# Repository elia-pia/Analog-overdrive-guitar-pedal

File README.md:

# A compact and easy-to-use analog overdrive guitar pedal.

## Images

Circuit schematic | PCB layout
--- | ---
 | 

## What is this?
 
this is a simple fully analog overdrive pedal that i designed personally, some of the graphics on the pcb are inspire by a Dean From Hell guitar

The goal was to create an affordable and straightforward guitar effect while learning more about analog electronics, audio circuits and PCB design.
it features one tl082 amplifier, two 1N§14B clipping diodes and three gain, tone, volume pots

## Features:

Fully analog signal processing.
TL082 dual operational amplifier.
Two 1N4148 clipping diodes.
Three adjustable controls: Gain, Tone and Volume.
Custom-designed PCB and circuit schematic.
Compact design suitable for a DIY guitar pedal enclosure.
Affordable and beginner-friendly construction.

## Building it

1. Order the PCB from JLCPCB using the KiCad project files.
2. you can build a case with simple household materials or buy a box from an hardware store
3. Assemble the PCB
4. put the pcb in the case

## Cost Estimate

The estimated cost of building one pedal is approximately $50 or less. Actual costs may vary depending on the PCB manufacturer, component availability, enclosure and shipping.

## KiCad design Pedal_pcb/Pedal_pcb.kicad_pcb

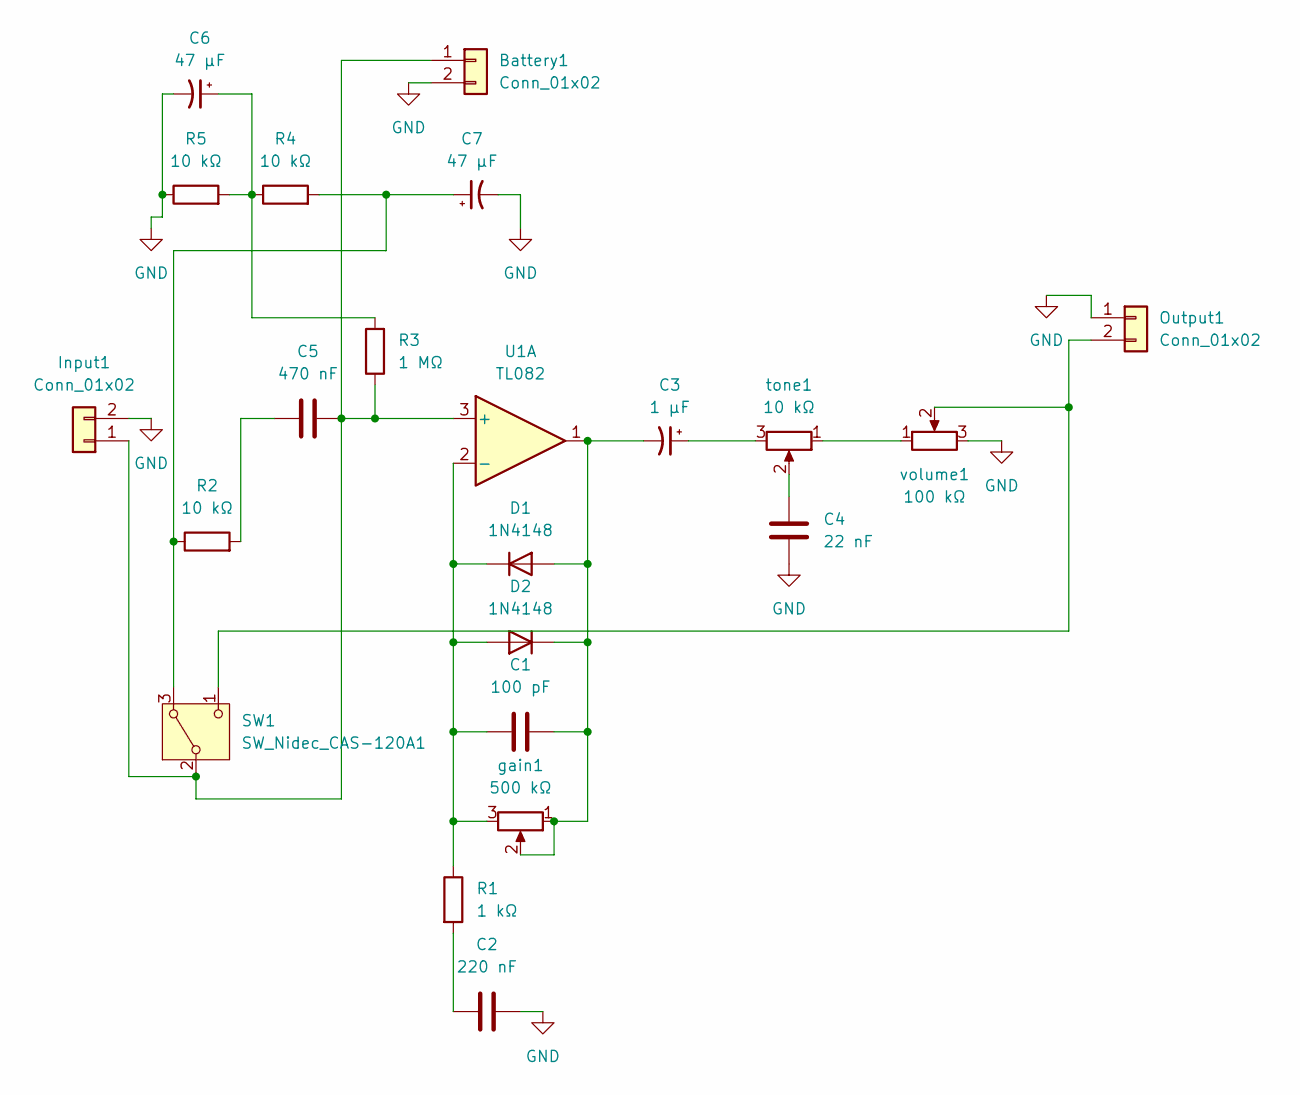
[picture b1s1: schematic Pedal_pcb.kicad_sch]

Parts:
Battery1: Conn_01x02; TestPoint_2Pads_Pitch2.54mm_Drill0.8mm
C1: 100 pF; C_Disc_D3.0mm_W1.6mm_P2.50mm
C2: 220 nF; C_Disc_D3.0mm_W1.6mm_P2.50mm
C3: 1 µF; CP_Radial_D5.0mm_P2.00mm
C4: 22 nF; C_Disc_D3.0mm_W1.6mm_P2.50mm
C5: 470 nF; C_Disc_D3.0mm_W1.6mm_P2.50mm
C6, C7: 47 µF; CP_Radial_D5.0mm_P2.00mm
D1, D2: 1N4148; D_DO-35_SOD27_P7.62mm_Horizontal
Input1: Conn_01x02; TestPoint_2Pads_Pitch2.54mm_Drill0.8mm
Output1: Conn_01x02; TestPoint_2Pads_Pitch2.54mm_Drill0.8mm
R1: 1 kΩ; R_Axial_DIN0207_L6.3mm_D2.5mm_P10.16mm_Horizontal
R2, R4, R5: 10 kΩ; R_Axial_DIN0207_L6.3mm_D2.5mm_P10.16mm_Horizontal
R3: 1 MΩ; R_Axial_DIN0207_L6.3mm_D2.5mm_P10.16mm_Horizontal
SW1: SW_Nidec_CAS-120A1; PinHeader_1x03_P2.54mm_Vertical
U1: TL082; DIP-8_W7.62mm
gain1: 500 kΩ; Potentiometer_Alpha_RD901F-40-00D_Single_Vertical
tone1: 10 kΩ; Potentiometer_Alpha_RD901F-40-00D_Single_Vertical
volume1: 100 kΩ; Potentiometer_Alpha_RD901F-40-00D_Single_Vertical

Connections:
GND: Battery1.2, C2.1, C4.2, C6.2, C7.2, Input1.2, Output1.1, R5.1, volume1.3
unnamed: Battery1.1, C5.2, Input1.1, R3.1, SW1.2 (B), U1.3 (+)
unnamed: C2.2, R1.2
unnamed: C3.1, tone1.3
unnamed: C4.1, tone1.2
unnamed: C5.1, R2.2
unnamed: C6.1, R3.2, R4.1, R5.2
unnamed: C1.1, C3.2, D1.2 (A), D2.1 (K), U1.1, gain1.1, gain1.2
unnamed: C1.2, D1.1 (K), D2.2 (A), R1.1, U1.2 (-), gain1.3
unnamed: Output1.2, SW1.1 (C), volume1.2
unnamed: C7.1, R2.1, R4.2, SW1.3 (A)
unnamed: tone1.1, volume1.1

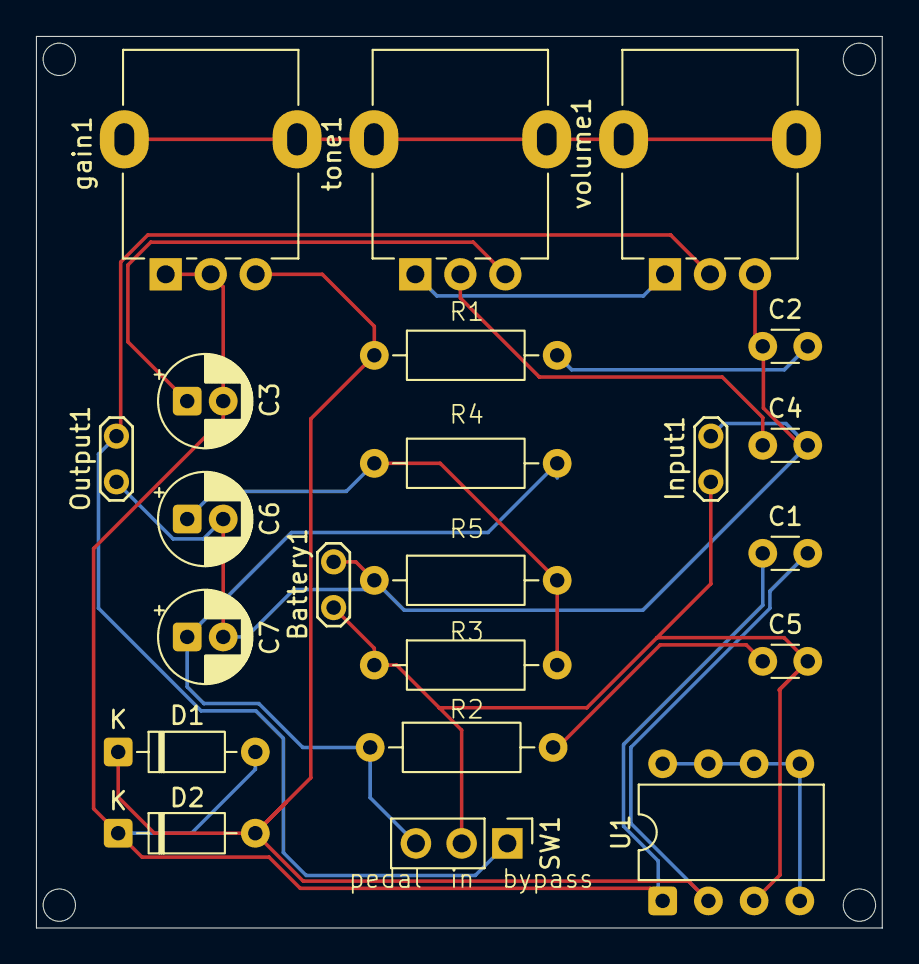
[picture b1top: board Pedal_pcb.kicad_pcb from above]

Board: 2 copper layers, 47.0 x 49.5 mm, 22 parts (0 on the bottom side), 12 nets.
